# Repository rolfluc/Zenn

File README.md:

# Zenn
Repo to house electrical designs for the Zenn.

# Precharge
Precharge will be conducted without a significant circuit board.

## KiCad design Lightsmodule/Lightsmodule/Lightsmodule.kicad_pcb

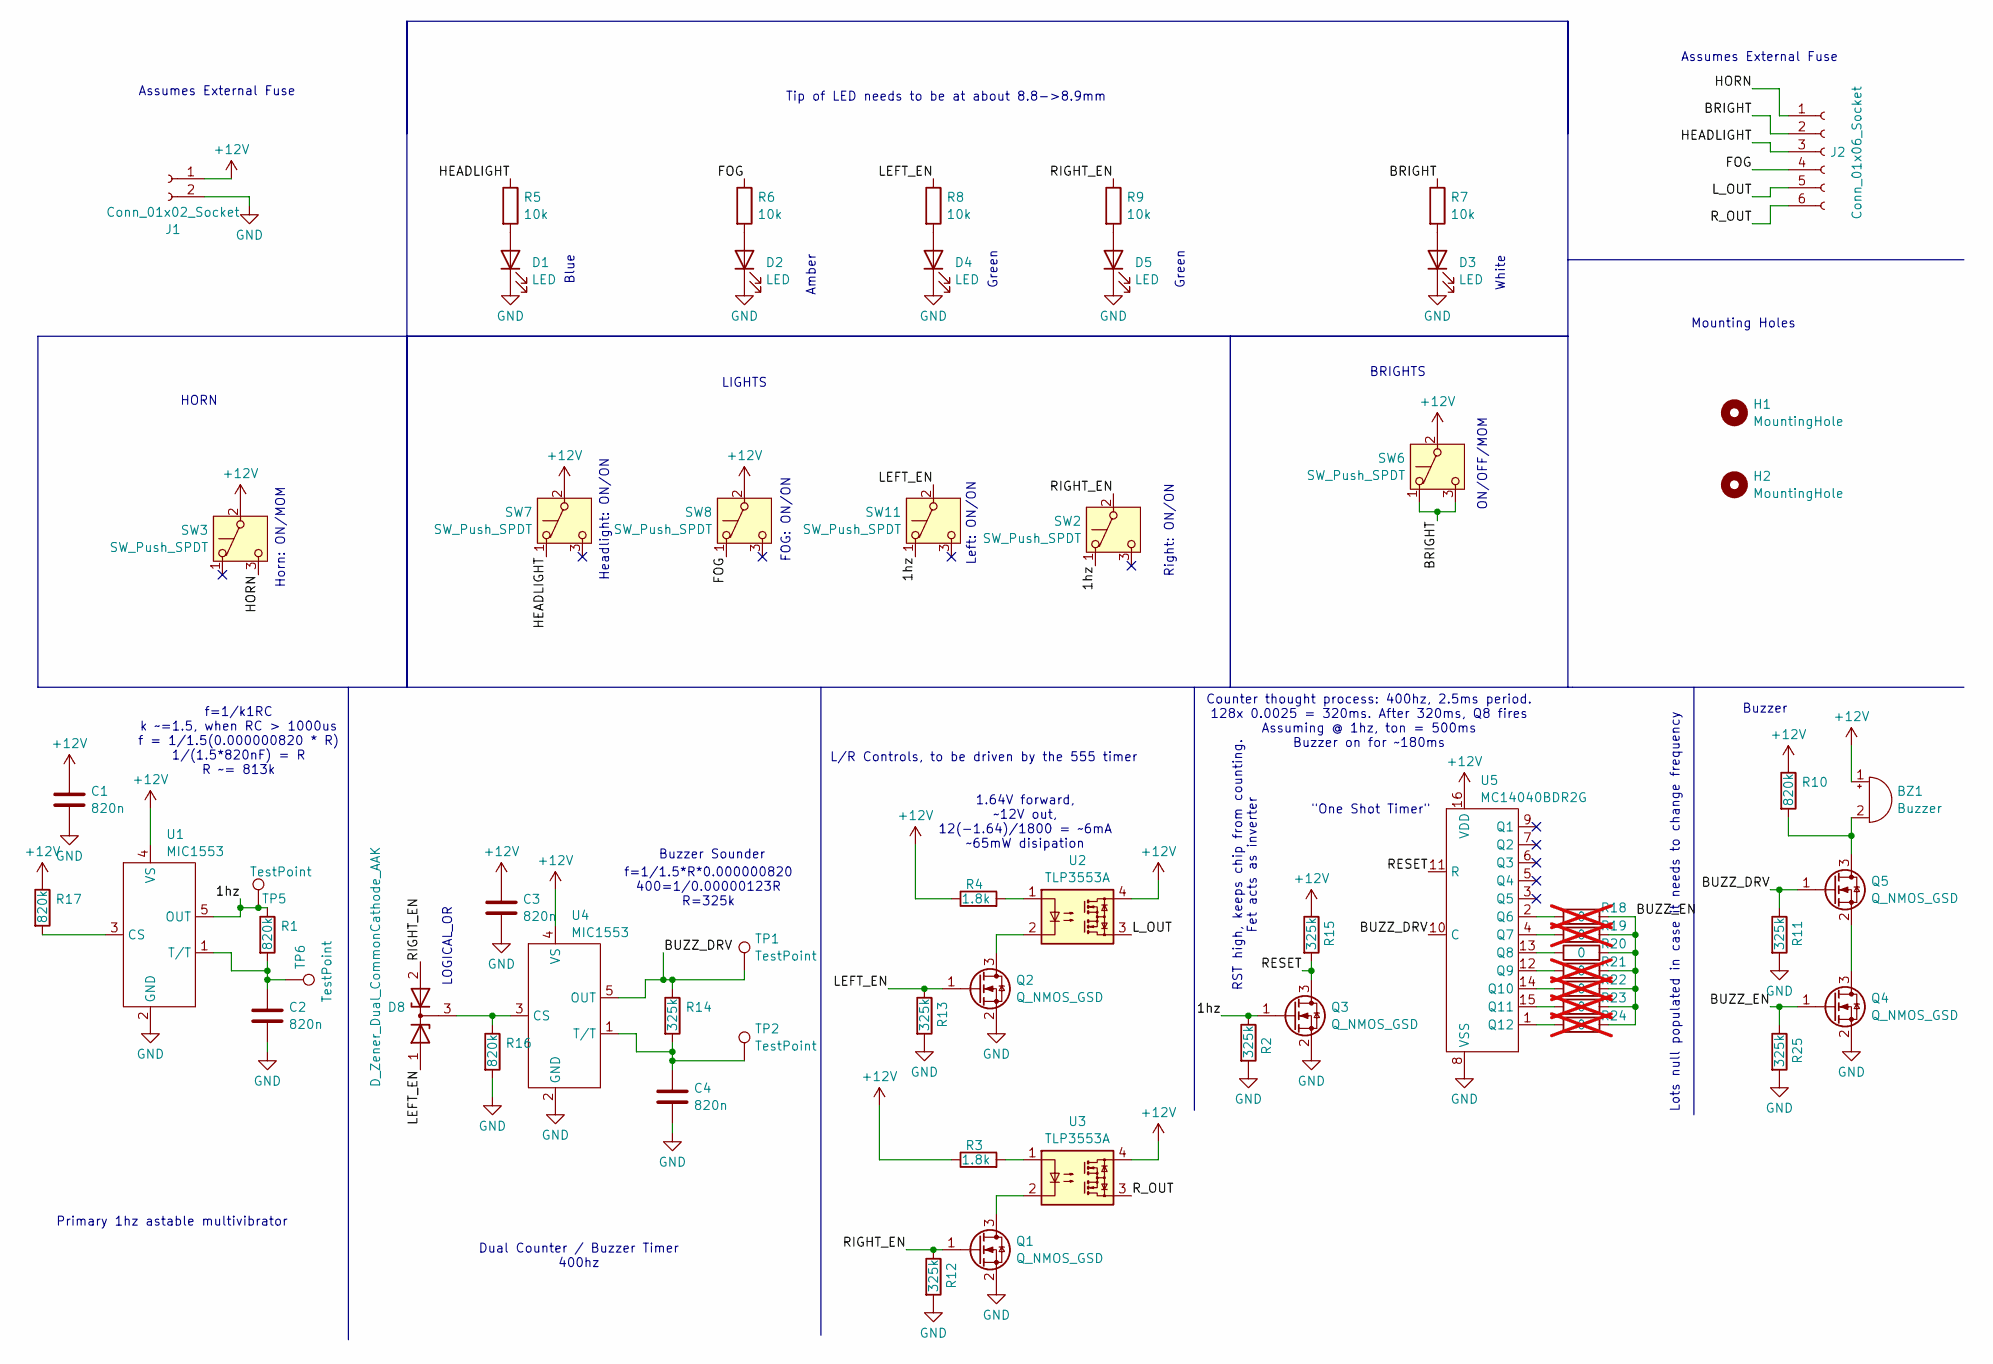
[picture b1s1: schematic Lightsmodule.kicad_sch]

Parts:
BZ1: Buzzer
C1, C2, C3, C4: 820n; C_0603_1608Metric
D1: LED; LED_D3.0mm; MPN WP710A10QBC/D
D2: LED; LED_D3.0mm; MPN WP710A10ND
D3: LED; LED_D3.0mm; MPN WP7104QWC/D
D4, D5: LED; LED_D3.0mm; MPN WP710A10LGD
D8: D_Zener_Dual_CommonCathode_AAK; SOT-23; MPN PMEG2005CT,215
H1, H2: MountingHole; MountingHole_4.3mm_M4
J1: Conn_01x02_Socket; CUI_TB002-500-02BE; MPN TB002-500-02BE
J2: Conn_01x06_Socket; CUI_TB002-500-06BE; MPN TB002-500-06BE
Q1, Q2, Q3, Q4, Q5: Q_NMOS_GSD; SOT-23; MPN DMN1019USN-13
R1, R10, R16, R17: 820k; R_0402_1005Metric
R2, R11, R12, R13, R15, R25: 325k; R_0402_1005Metric; MPN CRCW04022M00FKED
R3, R4: 1.8k; R_0603_1608Metric; MPN ERJ-PA3F1801V
R5, R6, R7, R8, R9: 10k; R_0402_1005Metric
R14: 325k; R_0402_1005Metric
R18, R19, R21, R22, R23, R24: 0; R_0402_1005Metric; not fitted
R20: 0; R_0402_1005Metric
SW2, SW7, SW8, SW11: SW_Push_SPDT; 100SPxT1B1M2QEH; MPN 100SP1T1B1M2QEH
SW3: SW_Push_SPDT; 100SPxT1B1M2QEH; MPN 100SP2T1B1M2QEH
SW6: SW_Push_SPDT; 100SPxT1B1M2QEH; MPN 100SP5T1B1M2QEH
TP1, TP2, TP5, TP6: TestPoint; TestPoint_Pad_1.0x1.0mm
U1, U4: MIC1553; SOT-23-5
U2, U3: TLP3553A; SOIC_3553ATP1_F_TOS
U5: MC14040BDR2G; SOIC-16_3.9x9.9mm_P1.27mm

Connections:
+12V: BZ1.1 (+), C1.1, C3.1, J1.1, R3.1, R4.1, R10.1, R15.1, R17.1, SW3.2 (B), SW6.2 (B), SW7.2 (B), SW8.2 (B), U1.4 (VS), U2.4, U3.4, U4.4 (VS), U5.16 (VDD)
/1hz: Q3.1 (G), R1.1, R2.1, SW2.1 (A), SW11.1 (A), TP5.1, U1.5 (OUT)
/BRIGHT: J2.2, R7.1, SW6.1 (A), SW6.3 (C)
/BUZZ_DRV: Q5.1 (G), R11.1, R14.1, TP1.1, U4.5 (OUT), U5.10 (C)
/BUZZ_EN: Q4.1 (G), R18.2, R19.2, R20.2, R21.2, R22.2, R23.2, R24.2, R25.1
/FOG: J2.4, R6.1, SW8.1 (A)
/HEADLIGHT: J2.3, R5.1, SW7.1 (A)
/HORN: J2.1, SW3.3 (C)
/LEFT_EN: D8.1 (A), Q2.1 (G), R8.1, R13.1, SW11.2 (B)
/L_OUT: J2.5, U2.3
/RESET: Q3.3 (D), R15.2, U5.11 (R)
/RIGHT_EN: D8.2 (A), Q1.1 (G), R9.1, R12.1, SW2.2 (B)
/R_OUT: J2.6, U3.3
GND: C1.2, C2.2, C3.2, C4.2, D1.1 (K), D2.1 (K), D3.1 (K), D4.1 (K), D5.1 (K), J1.2, Q1.2 (S), Q2.2 (S), Q3.2 (S), Q4.2 (S), R2.2, R11.2, R12.2, R13.2, R16.2, R25.2, U1.2 (GND), U4.2 (GND), U5.8 (VSS)
unnamed: BZ1.2 (-), Q5.3 (D), R10.2
unnamed: D1.2 (A), R5.2
unnamed: D2.2 (A), R6.2
unnamed: D3.2 (A), R7.2
unnamed: D4.2 (A), R8.2
unnamed: D5.2 (A), R9.2
unnamed: D8.3 (K), R16.1, U4.3 (CS)
unnamed: Q1.3 (D), U3.2
unnamed: Q2.3 (D), U2.2
unnamed: Q4.3 (D), Q5.2 (S)
unnamed: R3.2, U3.1
unnamed: R4.2, U2.1
unnamed: R17.2, U1.3 (CS)
unnamed: C2.1, R1.2, TP6.1, U1.1 (T/T)
unnamed: C4.1, R14.2, TP2.1, U4.1 (T/T)
unnamed: R18.1, U5.2 (Q6)
unnamed: R19.1, U5.4 (Q7)
unnamed: R20.1, U5.13 (Q8)
unnamed: R21.1, U5.12 (Q9)
unnamed: R22.1, U5.14 (Q10)
unnamed: R23.1, U5.15 (Q11)
unnamed: R24.1, U5.1 (Q12)

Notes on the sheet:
HORN
Assumes External Fuse
1.64V forward, ~12V out, 12(-1.64)/1800 = ~6mA ~65mW disipation
Blue
ON/OFF/MOM
FOG: ON/ON
"One Shot Timer"
RST high, keeps chip from counting. Fet acts as inverter
Buzzer Sounder
LOGICAL_OR
Primary 1hz astable multivibrator
Left: ON/ON
Green
Headlight: ON/ON
Tip of LED needs to be at about 8.8->8.9mm
BRIGHTS
L/R Controls, to be driven by the 555 timer
f=1/k1RC k ~=1.5, when RC > 1000us f = 1/1.5(0.000000820 * R) 1/(1.5*820nF) = R R ~= 813k
Counter thought process: 400hz, 2.5ms period. 128x 0.0025 = 320ms. After 320ms, Q8 fires Assuming @ 1hz, ton = 500ms Buzzer on for ~180ms
Amber
Horn: ON/MOM
f=1/1.5*R*0.000000820 400=1/0.00000123R R=325k
LIGHTS
Buzzer
White
Mounting Holes
Dual Counter / Buzzer Timer 400hz
Lots null populated in case it needs to change frequency
Right: ON/ON

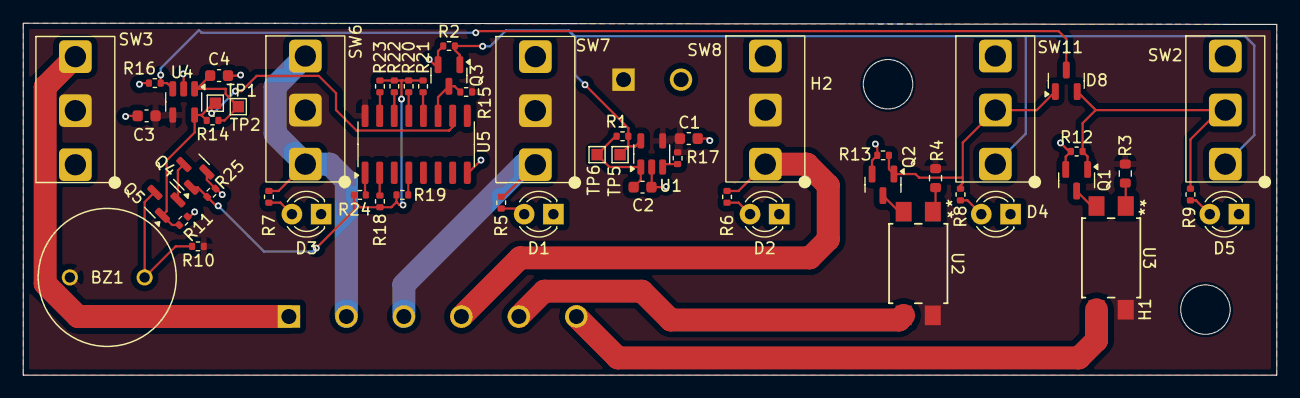
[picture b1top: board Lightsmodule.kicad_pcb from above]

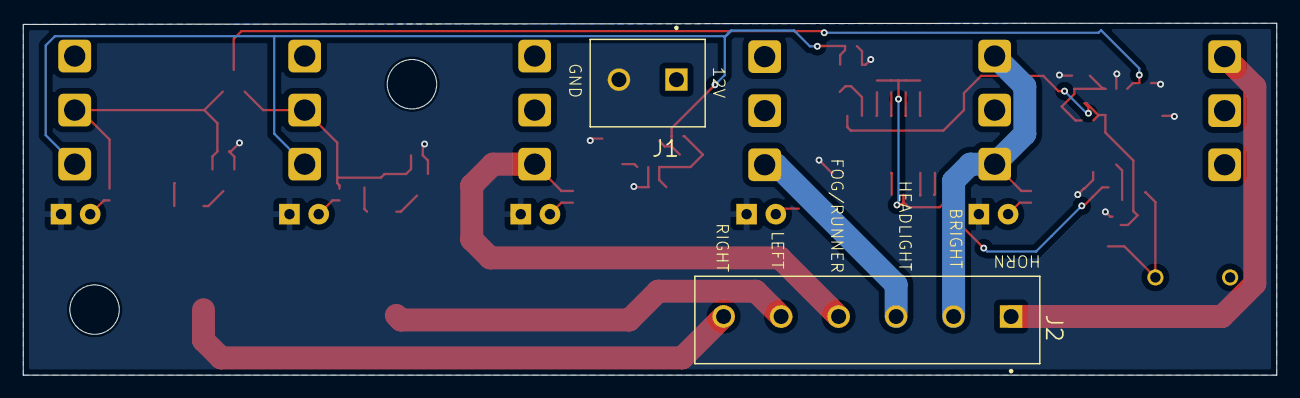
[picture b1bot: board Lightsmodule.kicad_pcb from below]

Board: 2 copper layers, 109.0 x 30.6 mm, 60 parts (2 on the bottom side), 36 nets.

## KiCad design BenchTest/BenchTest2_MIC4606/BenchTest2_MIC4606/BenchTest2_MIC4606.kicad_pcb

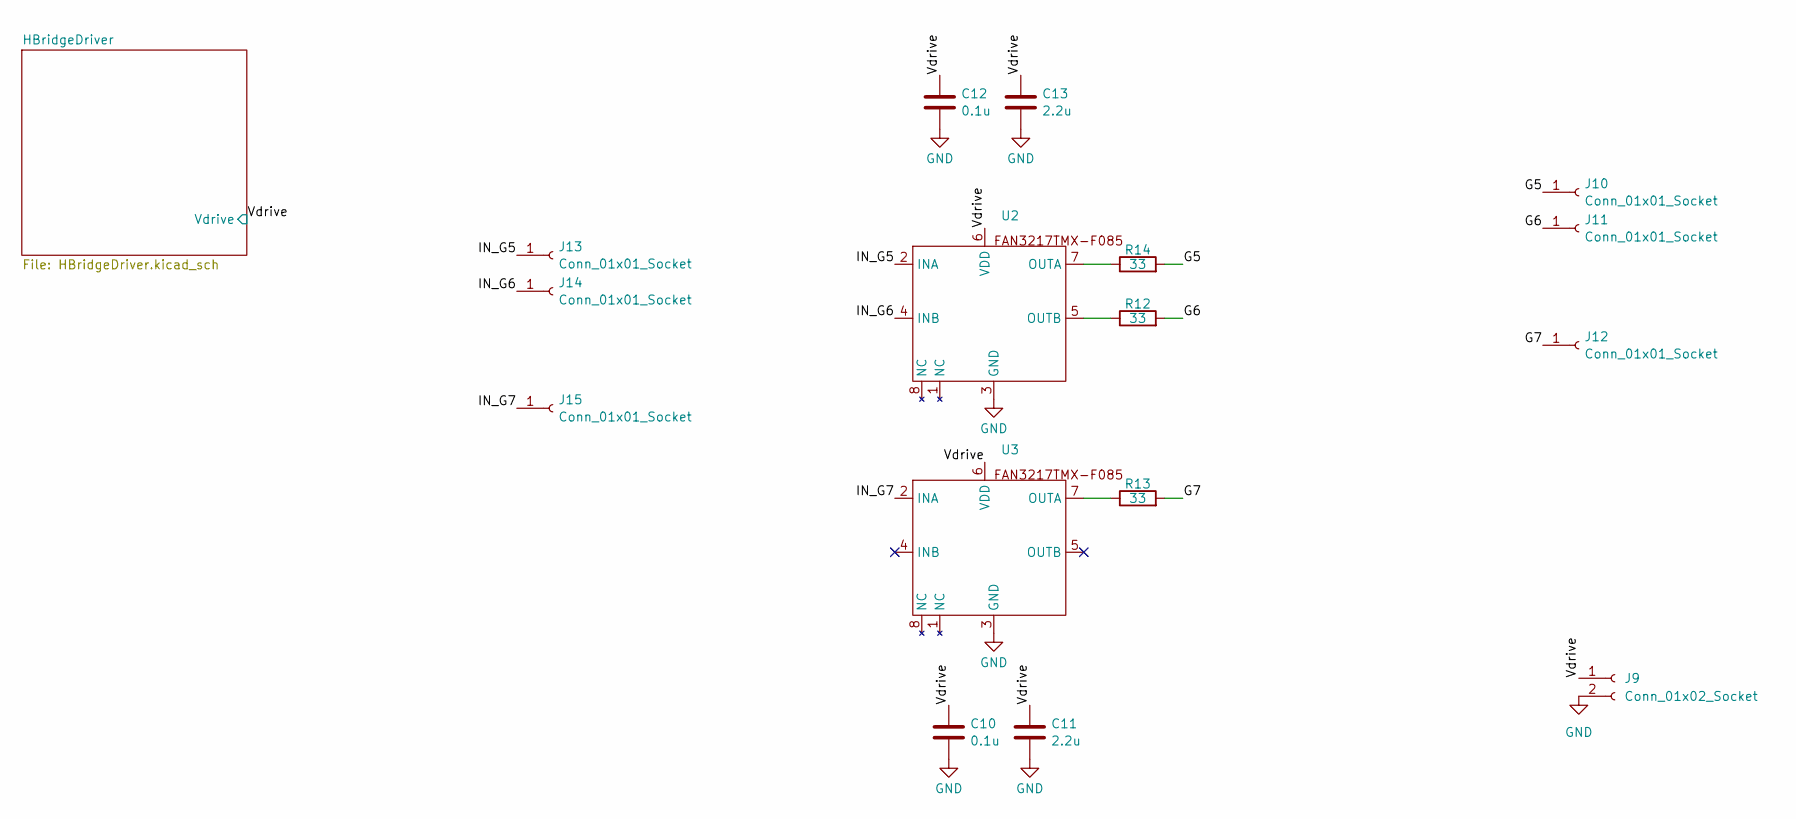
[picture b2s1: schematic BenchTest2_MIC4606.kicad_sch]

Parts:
C10, C12: 0.1u; C_0402_1005Metric_Pad0.74x0.62mm_HandSolder
C11, C13: 2.2u; C_0603_1608Metric_Pad1.08x0.95mm_HandSolder
J9: Conn_01x02_Socket; PinHeader_1x02_P2.54mm_Vertical
J10, J11, J12, J13, J14, J15: Conn_01x01_Socket; PinHeader_1x01_P2.54mm_Vertical
R12, R13, R14: 33; R_0402_1005Metric_Pad0.72x0.64mm_HandSolder
U2, U3: SOIC-8_3.9x4.9mm_P1.27mm

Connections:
/G5: J10.1, R14.2
/G6: J11.1, R12.2
/G7: J12.1, R13.2
/IN_G5: J13.1, U2.2 (INA)
/IN_G6: J14.1, U2.4 (INB)
/IN_G7: J15.1, U3.2 (INA)
/Vdrive: C10.1, C11.1, C12.1, C13.1, J9.1, U2.6 (VDD), U3.6 (VDD); also elsewhere on the board
GND: C10.2, C11.2, C12.2, C13.2, J9.2, U2.3 (GND), U3.3 (GND); also elsewhere on the board
unnamed: R14.1, U2.7 (OUTA)
unnamed: R12.1, U2.5 (OUTB)
unnamed: R13.1, U3.7 (OUTA)

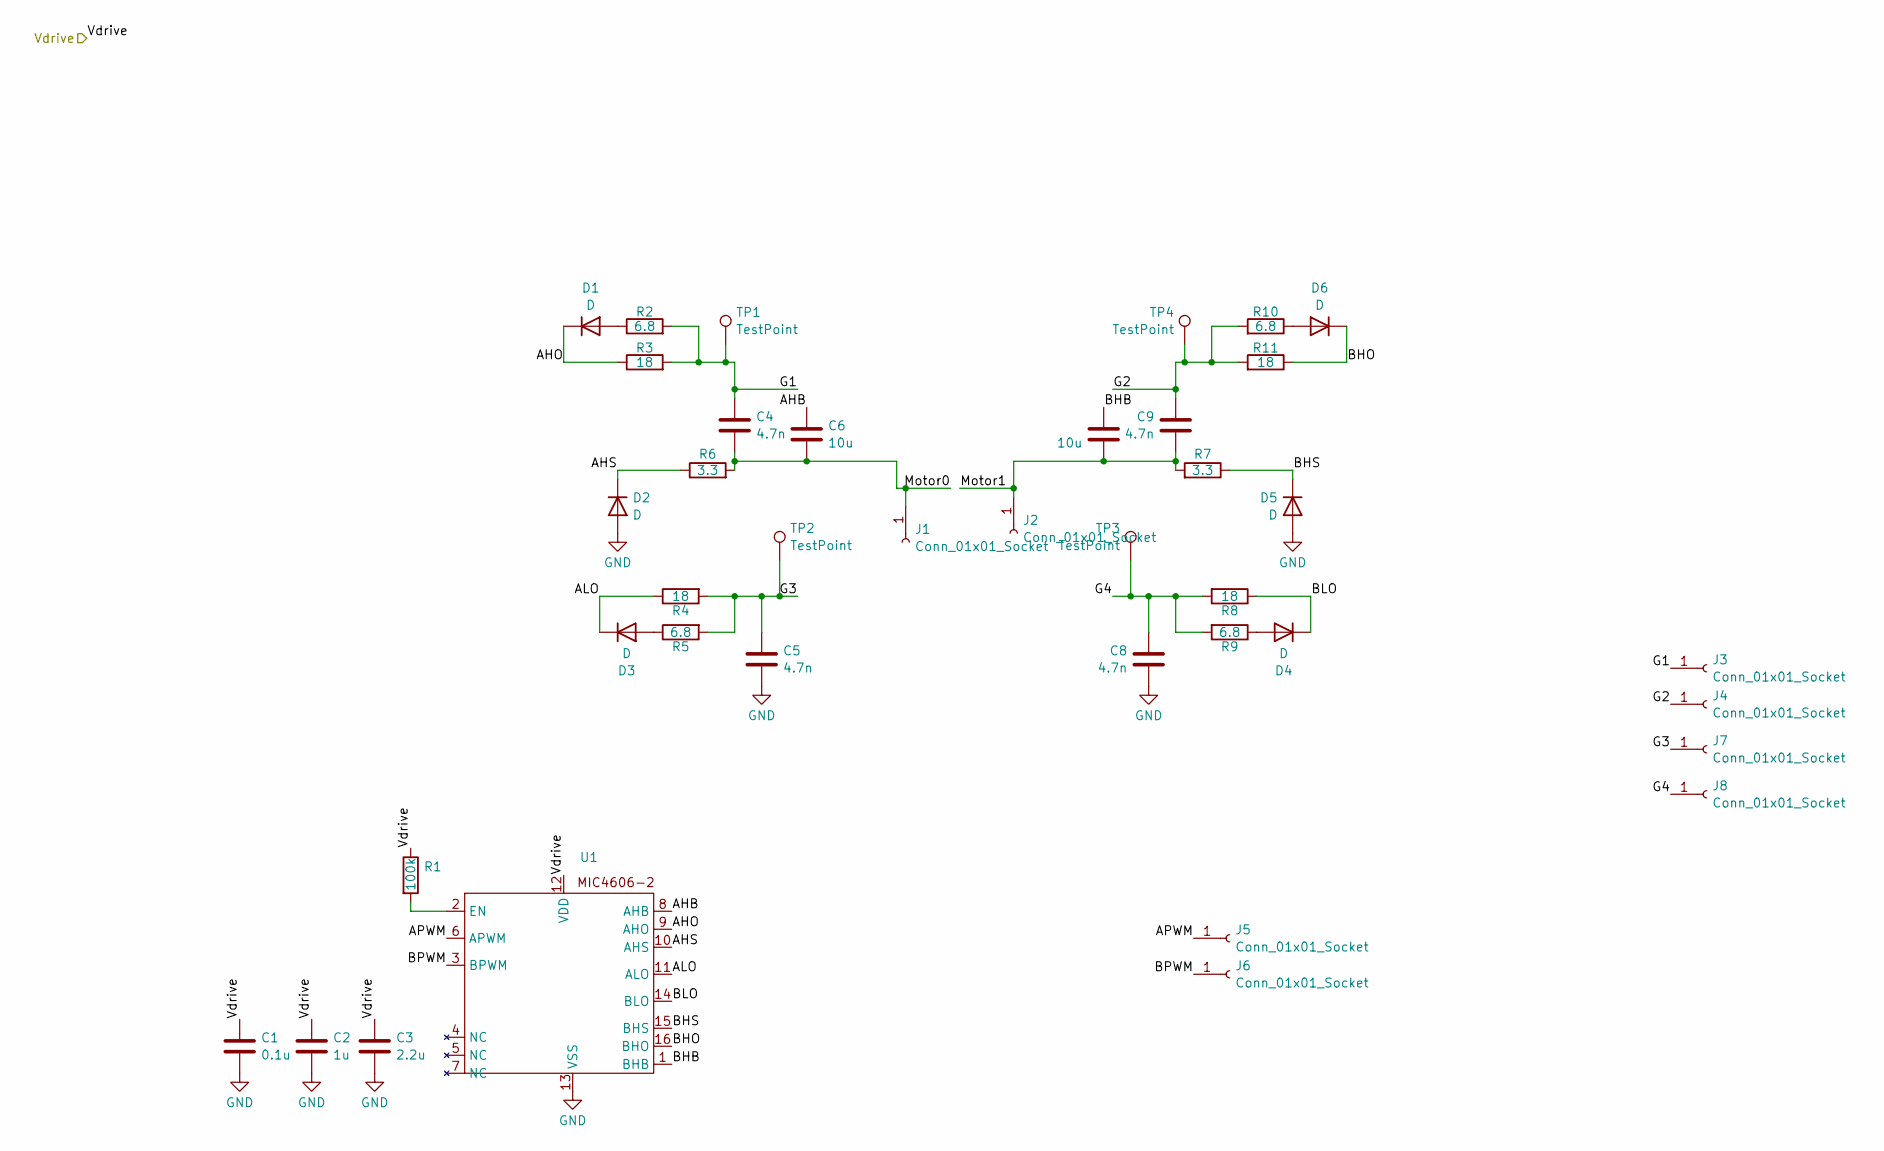
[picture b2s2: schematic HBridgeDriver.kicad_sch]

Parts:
C1: 0.1u; C_0402_1005Metric_Pad0.74x0.62mm_HandSolder
C2: 1u; C_0603_1608Metric_Pad1.08x0.95mm_HandSolder
C3: 2.2u; C_0603_1608Metric_Pad1.08x0.95mm_HandSolder
C4, C5, C8, C9: 4.7n; C_0805_2012Metric_Pad1.18x1.45mm_HandSolder
C6, C7: 10u; C_0805_2012Metric_Pad1.18x1.45mm_HandSolder
D1, D2, D3, D4, D5, D6: D; D_SOD-123F
J1, J2, J3, J4, J5, J6, J7, J8: Conn_01x01_Socket; PinHeader_1x01_P2.54mm_Vertical
R1: 100k; R_0402_1005Metric_Pad0.72x0.64mm_HandSolder
R2, R5, R9, R10: 6.8; R_0805_2012Metric_Pad1.20x1.40mm_HandSolder
R3, R4, R8, R11: 18; R_0805_2012Metric_Pad1.20x1.40mm_HandSolder
R6, R7: 3.3; R_0805_2012Metric_Pad1.20x1.40mm_HandSolder
TP1, TP2, TP3, TP4: TestPoint; TestPoint_Pad_1.0x1.0mm
U1: TSSOP-16_4.4x5mm_P0.65mm

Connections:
/HBridgeDriver/AHB: C6.1, U1.8 (AHB)
/HBridgeDriver/AHO: D1.1 (K), R3.1, U1.9 (AHO)
/HBridgeDriver/AHS: D2.1 (K), R6.1, U1.10 (AHS)
/HBridgeDriver/ALO: D3.1 (K), R4.1, U1.11 (ALO)
/HBridgeDriver/APWM: J5.1, U1.6 (APWM)
/HBridgeDriver/BHB: C7.1, U1.1 (BHB)
/HBridgeDriver/BHO: D6.1 (K), R11.1, U1.16 (BHO)
/HBridgeDriver/BHS: D5.1 (K), R7.1, U1.15 (BHS)
/HBridgeDriver/BLO: D4.1 (K), R8.1, U1.14 (BLO)
/HBridgeDriver/BPWM: J6.1, U1.3 (BPWM)
/HBridgeDriver/G1: C4.1, J3.1, R2.2, R3.2, TP1.1
/HBridgeDriver/G2: C9.1, J4.1, R10.2, R11.2, TP4.1
/HBridgeDriver/G3: C5.1, J7.1, R4.2, R5.2, TP2.1
/HBridgeDriver/G4: C8.1, J8.1, R8.2, R9.2, TP3.1
/HBridgeDriver/Motor0: C4.2, C6.2, J1.1, R6.2
/HBridgeDriver/Motor1: C7.2, C9.2, J2.1, R7.2
/Vdrive: C1.1, C2.1, C3.1, R1.1, U1.12 (VDD); also elsewhere on the board
GND: C1.2, C2.2, C3.2, C5.2, C8.2, D2.2 (A), D5.2 (A), U1.13 (VSS); also elsewhere on the board
unnamed: D1.2 (A), R2.1
unnamed: D3.2 (A), R5.1
unnamed: D4.2 (A), R9.1
unnamed: D6.2 (A), R10.1
unnamed: R1.2, U1.2 (EN)

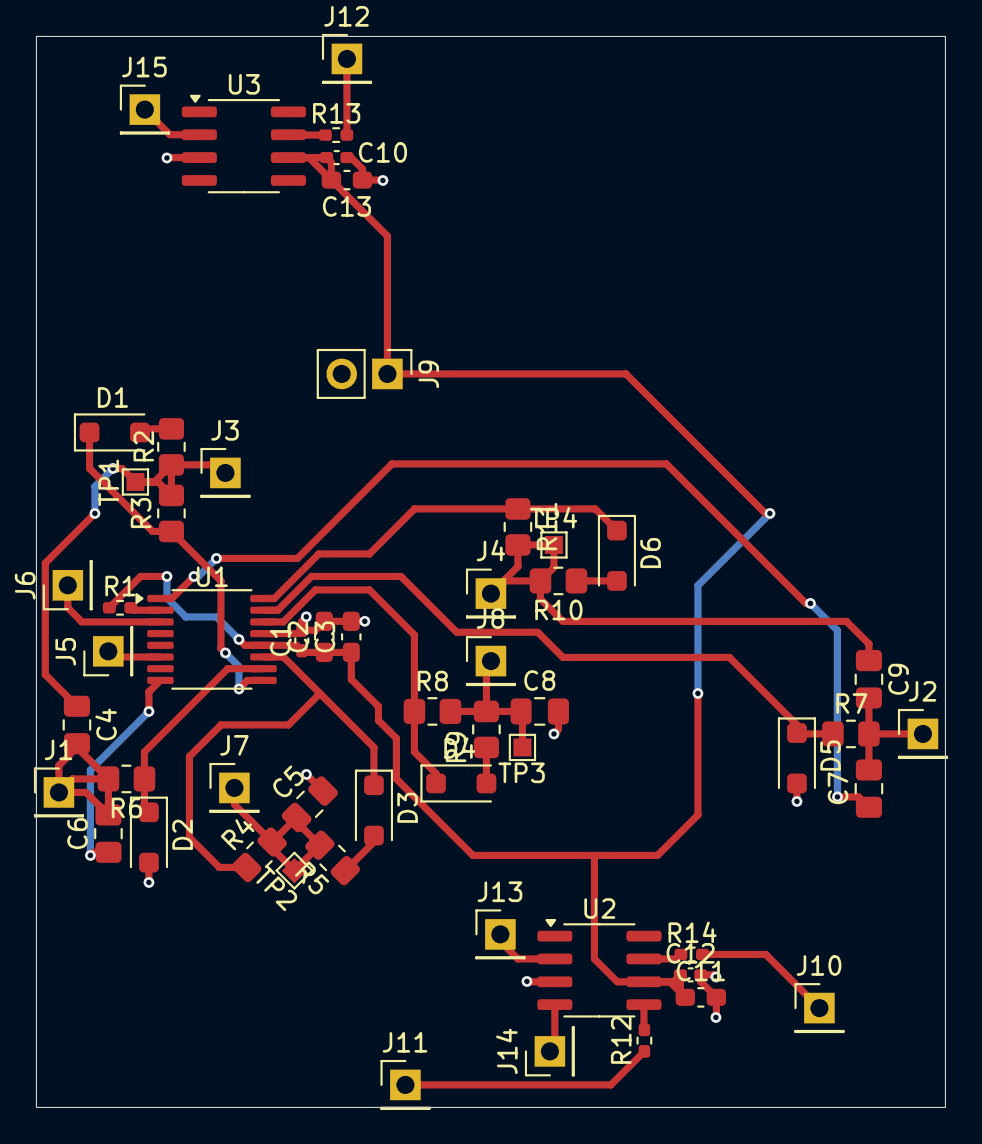
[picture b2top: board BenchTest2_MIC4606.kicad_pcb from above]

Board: 2 copper layers, 50.5 x 59.5 mm, 55 parts (0 on the bottom side), 32 nets.

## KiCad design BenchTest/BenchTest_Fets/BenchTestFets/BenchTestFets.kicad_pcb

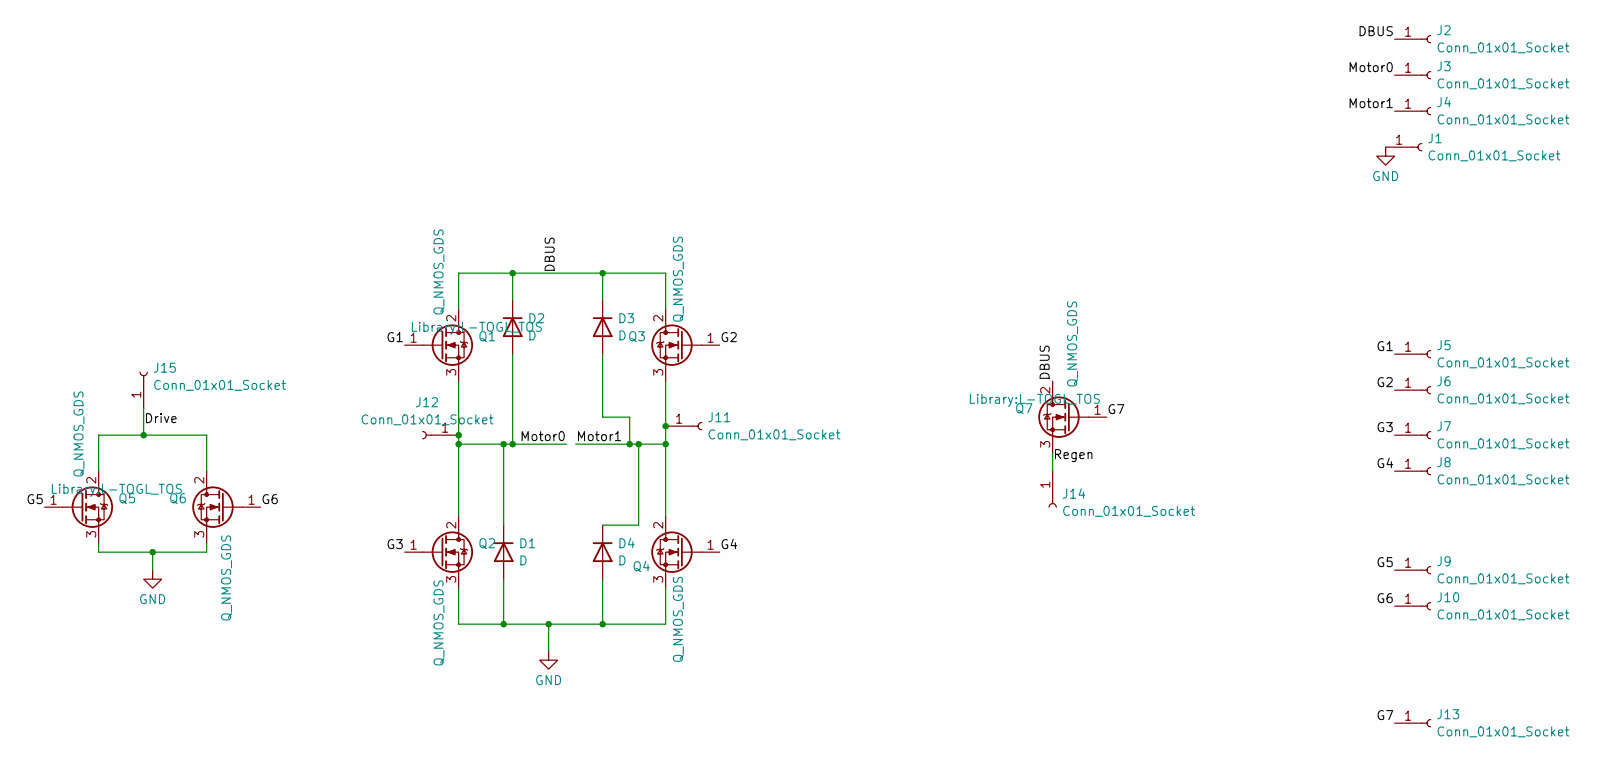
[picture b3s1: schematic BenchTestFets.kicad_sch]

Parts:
D1, D2, D3, D4: D; D_SOD-123F
J1, J2, J3, J4, J14, J15: Conn_01x01_Socket; Wuerth_REDCUBE-THR_WP-THRSH_74651194_THR
J5, J6, J7, J8, J9, J10, J11, J12, J13: Conn_01x01_Socket; PinHeader_1x01_P2.54mm_Vertical
Q1, Q2, Q3, Q4, Q5, Q6, Q7: Q_NMOS_GDS; L-TOGL_TOS

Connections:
/DBUS: D2.1 (K), D3.1 (K), J2.1, Q1.2 (D), Q3.2 (D), Q7.2 (D)
/Drive: J15.1, Q5.2 (D), Q6.2 (D)
/G1: J5.1, Q1.1 (G)
/G2: J6.1, Q3.1 (G)
/G3: J7.1, Q2.1 (G)
/G4: J8.1, Q4.1 (G)
/G5: J9.1, Q5.1 (G)
/G6: J10.1, Q6.1 (G)
/G7: J13.1, Q7.1 (G)
/Motor0: D1.1 (K), D2.2 (A), J3.1, J12.1, Q1.3 (S), Q2.2 (D)
/Motor1: D3.2 (A), D4.1 (K), J4.1, J11.1, Q3.3 (S), Q4.2 (D)
/Regen: J14.1, Q7.3 (S)
GND: D1.2 (A), D4.2 (A), J1.1, Q2.3 (S), Q4.3 (S), Q5.3 (S), Q6.3 (S)

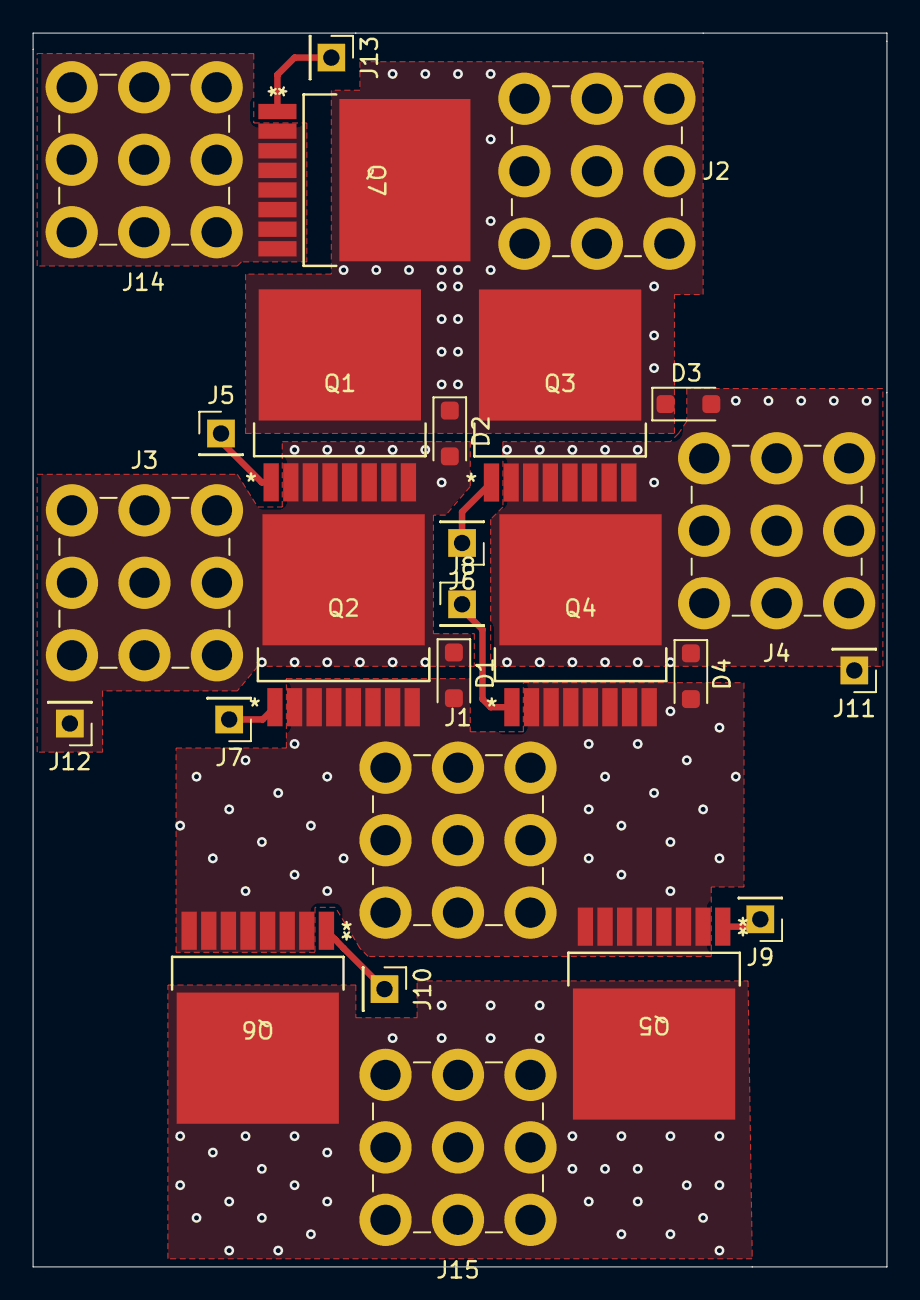
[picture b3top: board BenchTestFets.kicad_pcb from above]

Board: 2 copper layers, 52.2 x 75.5 mm, 26 parts (0 on the bottom side), 13 nets.

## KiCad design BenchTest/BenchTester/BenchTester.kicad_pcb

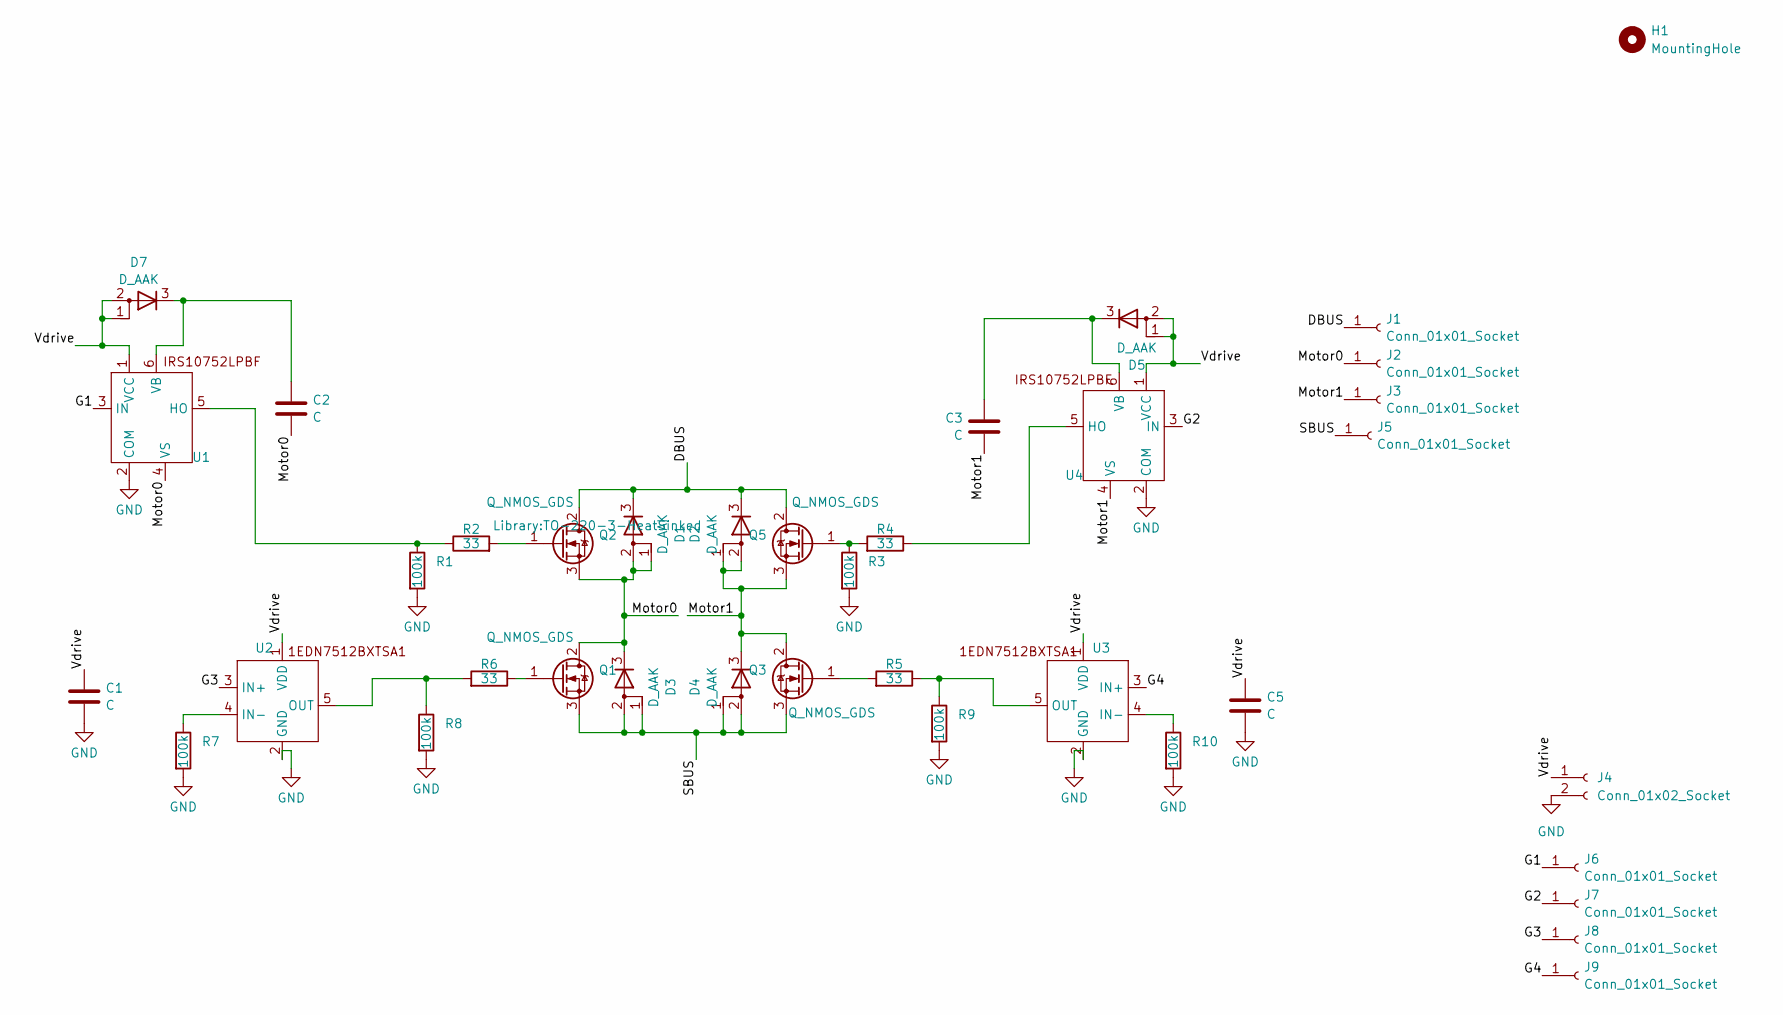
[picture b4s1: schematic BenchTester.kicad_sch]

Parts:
C1, C2, C3, C5: C; C_0805_2012Metric
D1, D2, D3, D4, D5, D7: D_AAK; TO-252-2_SBR20M150D1Q
H1: MountingHole; MountingHole_3.2mm_M3
J1, J2, J3, J5: Conn_01x01_Socket; Wuerth_REDCUBE-THR_WP-THRSH_74651194_THR
J4: Conn_01x02_Socket; PinHeader_1x02_P2.54mm_Vertical
J6, J7, J8, J9: Conn_01x01_Socket; PinHeader_1x01_P2.54mm_Vertical
Q1, Q2, Q3, Q5: Q_NMOS_GDS; TO-220-3-HeatSinked
R1, R3, R7, R8, R9, R10: 100k; R_0402_1005Metric
R2, R4, R5, R6: 33; R_0402_1005Metric
U1, U4: SOT-23-6_Handsoldering
U2, U3: SC-74A-5_1.55x2.9mm_P0.95mm

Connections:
/DBUS: D1.3 (K), D2.3 (K), J1.1, Q2.2 (D), Q5.2 (D)
/G1: J6.1, U1.3 (IN)
/G2: J7.1, U4.3 (IN)
/G3: J8.1, U2.3 (IN+)
/G4: J9.1, U3.3 (IN+)
/Motor0: C2.2, D1.1 (A), D1.2 (A), D3.3 (K), J2.1, Q1.2 (D), Q2.3 (S), U1.4 (VS)
/Motor1: C3.2, D2.1 (A), D2.2 (A), D4.3 (K), J3.1, Q3.2 (D), Q5.3 (S), U4.4 (VS)
/SBUS: D3.1 (A), D3.2 (A), D4.1 (A), D4.2 (A), J5.1, Q1.3 (S), Q3.3 (S)
/Vdrive: C1.1, C5.1, D5.1 (A), D5.2 (A), D7.1 (A), D7.2 (A), J4.1, U1.1 (VCC), U2.1 (VDD), U3.1 (VDD), U4.1 (VCC)
GND: C1.2, C5.2, J4.2, R1.2, R3.2, R7.2, R8.2, R9.2, R10.2, U1.2 (COM), U2.2 (GND), U3.2 (GND), U4.2 (COM)
unnamed: C3.1, D5.3 (K), U4.6 (VB)
unnamed: C2.1, D7.3 (K), U1.6 (VB)
unnamed: Q1.1 (G), R6.1
unnamed: Q2.1 (G), R2.2
unnamed: Q3.1 (G), R5.2
unnamed: Q5.1 (G), R3.1, R4.2
unnamed: R1.1, R2.1, U1.5 (HO)
unnamed: R7.1, U2.4 (IN-)
unnamed: R6.2, R8.1, U2.5 (OUT)
unnamed: R10.1, U3.4 (IN-)
unnamed: R5.1, R9.1, U3.5 (OUT)
unnamed: R4.1, U4.5 (HO)

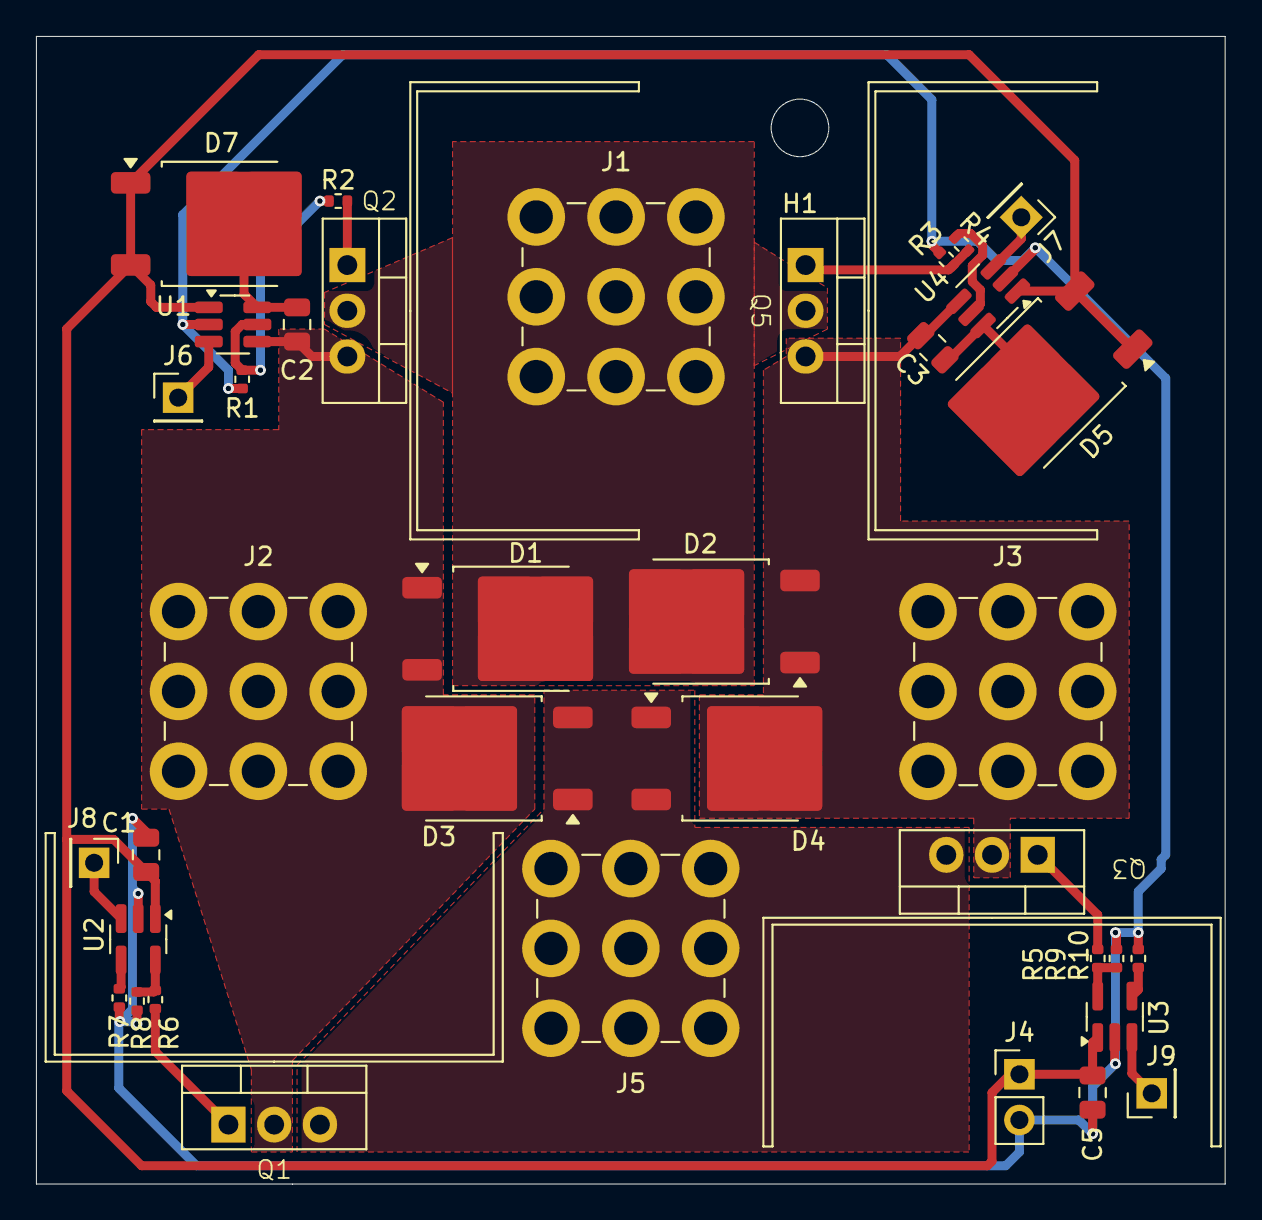
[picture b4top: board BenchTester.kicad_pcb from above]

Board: 2 copper layers, 66.0 x 63.8 mm, 38 parts (0 on the bottom side), 22 nets.

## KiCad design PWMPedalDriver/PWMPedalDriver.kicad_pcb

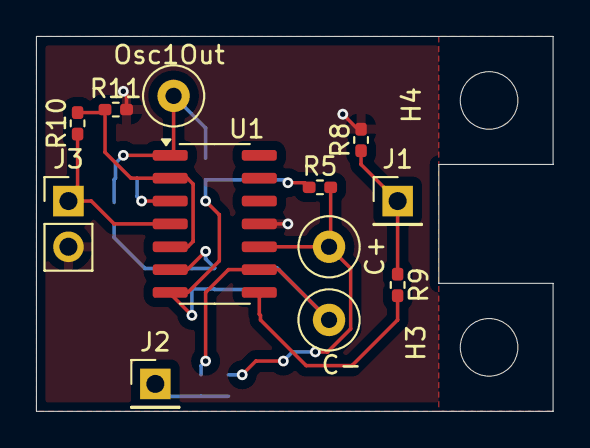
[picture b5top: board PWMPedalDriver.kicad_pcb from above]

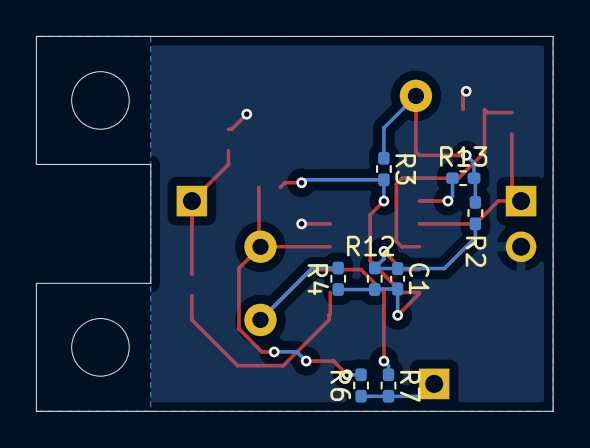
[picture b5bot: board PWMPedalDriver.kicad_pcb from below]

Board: 2 copper layers, 28.7 x 20.8 mm, 22 parts (8 on the bottom side), 12 nets.

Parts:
C1: 400n; C_0402_1005Metric_Pad0.74x0.62mm_HandSolder
C+: TestPoint; TestPoint_Loop_D2.60mm_Drill0.9mm_Beaded
C-: TestPoint; TestPoint_Loop_D2.60mm_Drill0.9mm_Beaded
H3, H4: MountingHole; MountingHole_3.2mm_M3
J1, J2: Conn_01x01_Pin; PinHeader_1x01_P2.54mm_Vertical
J3: Conn_01x02_Pin; PinHeader_1x02_P2.54mm_Vertical
Osc1Out: TestPoint; TestPoint_Loop_D2.60mm_Drill0.9mm_Beaded
R2, R13: 10k; R_0402_1005Metric_Pad0.72x0.64mm_HandSolder
R3: 4k; R_0402_1005Metric_Pad0.72x0.64mm_HandSolder
R4, R5, R6, R7, R9: 0; R_0402_1005Metric_Pad0.72x0.64mm_HandSolder
R8: 100k; R_0402_1005Metric_Pad0.72x0.64mm_HandSolder
R10, R11: 50k; R_0402_1005Metric_Pad0.72x0.64mm_HandSolder
R12: 100k_NP; R_0402_1005Metric_Pad0.72x0.64mm_HandSolder
U1: LM324; SOIC-14_3.9x8.7mm_P1.27mm

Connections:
/AnalogIn: J2.1, R6.1, R7.2
/Ref: R10.2, R11.1, U1.2 (-), U1.5 (+)
/VCC: J3.1, R10.1, U1.4 (V+)
GND: J3.2, R8.2, R11.2, U1.11 (V-)
unnamed: C1.2, R3.2, R4.1, R5.1, R12.2, U1.7
unnamed: J1.1, R8.1, R9.1
unnamed: Osc1Out.1, R2.1, R3.1, R13.2, U1.1
unnamed: R9.2, U1.8
unnamed: R13.1, U1.3 (+)
unnamed: C1.1, R2.2, R12.1, U1.6 (-)
unnamed: C+.1, R5.2, R6.2, U1.10 (+)
unnamed: C-.1, R4.2, R7.1, U1.9 (-)

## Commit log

2025-03-13 Adding H Bridge Design
2025-03-14 WIP for Zenn motor controller
2025-03-15 Simulated Triangle -> PWM Driver.
2025-03-15 PCB Layout Start
2025-03-15 First pass placement
2025-03-16 Potential Routing / Placement for PWM
2025-03-16 WIP - Diode / major parts assignment.
2025-03-17 Basic Incomplete placement
2025-03-17 Initial Placement
2025-03-17 Grouping Near Complete
    Grouping of components is close to complete. Next is placement near
    respective other groups. Need Full Footprint for FET with heatsink
    before completing that exercise.
2025-03-22 Shipped Board
    Shipped out the Analog -> PWM driver
2025-03-22 Footprint assignment
    Footprint assignment for Fets.
2025-03-22 Re-placement of positions to reduce trace length
2025-03-22 Potential Layout
2025-03-22 Board Layout
2025-03-22 Post DRC
2025-03-30 Existing Board Design, and Indicator Layout
    May need to re-adjust the indicators, but WIP.
    Also need to get back panel aligned.
2025-03-30 Quick Fix on Mounting Bracket
2025-03-30 Close Placement of Motors. Need Mechanical Fit check first
2025-04-12 Removing PWM Driver. New thought process as this is no longer needed.
2025-04-12 WIP - Test build for the Stepper Driver
2025-04-12 Starting Bottom Indicator
2025-04-13 Board Outline Lain out, needs testing.
2025-04-14 User1/2 Outline for image placement
2025-04-14 Added Dickbutt
2025-04-15 Some placements, adding plastic inserts.
2025-04-15 Adding SVGs Imported.
2025-04-15 Added all SVGs imported. Need to invert all.
2025-04-15 New SVGs
2025-04-15 Placement and positioning of icons
2025-04-16 Proper Layout
2025-04-16 Minor change
2025-04-16 Minor Silkscreen Adjustments
2025-04-17 LEDs outlined. Colors Chosen.
2025-04-18 WIP checkin
2025-04-18 Starting Main Controller
2025-04-19 Added Buzzer, Fet Footprint, and pulled backlighting
2025-04-20 WIP - Starting Voltage Measurement
2025-04-20 WIP - HV measurement may be done
2025-04-20 WIP likely need to switch 12V signalling around
2025-04-20 Adding Motor Controller Page
2025-04-20 Adding Labels for Switches
2025-04-20 Added Polyfuse
2025-05-06 Removing Errant Silkscreen
2025-05-11 Mechanicals, and STM32Project
2025-05-11 Ignoring PDFs
2025-05-11 Project building
2025-05-11 FreeRTOS is now building
    Adding Heartbeat as well.
2025-05-11 FreeRTOS / HB working, just poor timing
    half second is closer to 2.5s.
2025-05-11 Working Timebase / Systick. heartbeat right
2025-05-11 Backlight Starting
2025-05-12 WIP - setting up Backlight Controller
2025-05-13 Schematic Outline, needs placement
2025-05-18 Creating Motor Interfacing, and Pin Defs for ADC and the project
2025-05-18 File Cleanup, Timer Updates for CBs
2025-05-18 Ordered Boards
2025-05-18 WIP - Creating Seperate board for controlling fet board
2025-05-19 Board to ship for Fets
2025-05-21 Motor Handle setup and potenital implementation for Timing
2025-05-21 LED Driver Start
2025-06-11 WIP - Partly working PWM for LED Driver
2025-06-11 Migrating LED Controller to task
2025-06-13 Functioning Workflow for ADC readings for Ambient
2025-06-13 ADC Implementation Complete
2025-06-13 CAN Start
2025-06-18 Timer accurate, Clock rate increase. Need TLC5973 adaptation for data
2025-06-19 Moving towards Task for Can implementation, Timing Update, Stepper working
2025-06-19 Starting Motor Controller
2025-07-03 Refactor for Motor Driving
2025-07-04 Mostly working homing, and motor timing in timer.
2025-07-08 CAN WIP
2025-07-15 ADC->PWM1 Synced. Need to do Master -> TIM1,2
2025-07-18 Mostly working PWM
    Still need better syncing, but made the tree work from Tim3->2,1
2025-07-20 Starting Migrating for better unified PWM
2025-07-20 Synced PWM signals working
2025-07-21 Working Analog / Switch intervace for driving the signals
2025-07-21 Minor update for small delay between samples
2025-07-22 Working Sample to drive
2025-10-31 Kicad V update
2025-10-31 WIP New Motor Design
2025-11-01 WIP - Further refinement
2025-11-06 H Bridge Continuation
2025-12-09 Defined Some parts, added notes for Arm/regen/H bridge
2025-12-09 Additional Documents / Routing
2025-12-13 Continued Connections, split board design
    Confirmed digital / motor board split
    Configured Connections appropriately. Assigned some footprints.
2025-12-13 Removed Optoisolators from digital Signals
    Will be requiring these on the drive side
2025-12-13 Assigned HP Footprints
2025-12-13 Starting Logic Board Domain
2025-12-17 Added Isolation for digital drives
2025-12-17 Added motor voltage measurement for regen
2025-12-17 Added VMOT Measurements
2025-12-17 Added Power Module for MCU
2025-12-18 WIP Controller in progress
    w
2025-12-18 Migrated to 5V drive from digital side
2025-12-19 Adapting Regen to be a Regen Heater
2026-01-04 Footprint / Capacitor Assignment
2026-01-04 Connector Footprints Assigned
2026-05-06 WIP Headlight Module. Simulated timing. Switches Chosen
2026-05-08 Board Layout and Assignment. Pending Buzzer
2026-05-14 In Theory working Timing / Buzzer Circuit
2026-05-14 First pass Layout
2026-05-14 Silkscreen Change, Minor layout for better planes
2026-05-14 New Layout based on more spread out Switches
2026-05-15 DRC Checked PCB. Shipped
2026-05-20 WIP Mechanical Housing for the Lights Module
